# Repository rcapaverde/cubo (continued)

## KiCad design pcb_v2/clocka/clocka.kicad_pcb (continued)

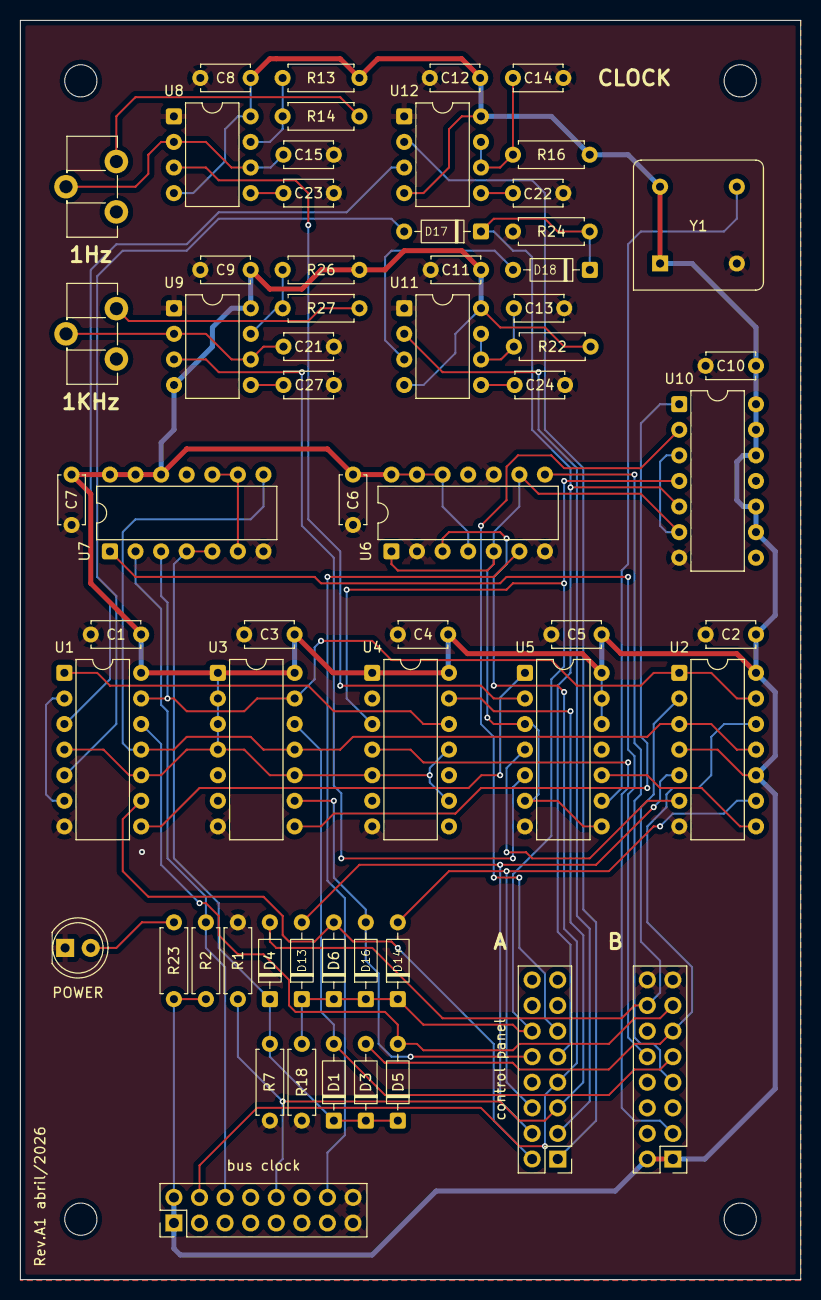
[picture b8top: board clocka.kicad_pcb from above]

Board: 2 copper layers, 77.5 x 125.0 mm, 61 parts (0 on the bottom side), 52 nets.

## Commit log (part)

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2025-12-11 arquivos que estavam no pc67
2025-12-11 interface serial
2025-12-12 arquivos no note
2025-12-12 arquivos do gdrive
2025-12-12 ignorar tambem os arquivos de backup do kicad
2025-12-14 adicionados o designador e o swap para a arquivo reg16
2025-12-21 alterando os pinos de alimentacao no conector
2025-12-23 projeto enviado para impressao em dezembro/25
2025-12-23 roteamento pronto e electric rules verificadas
2025-12-28 concluido o desenho das placas satelite do banco de registradores de 16 bits
2025-12-30 adicionados imagens 3D para os componentes customizados
2025-12-31 modelo 3d do interruptor; primeira versao do firmware do testbench (falta ainda converter o codigo para comunicar via latch)
2026-01-03 comunicacao com o LCD agora eh feita de forma direta, sem o uso de bibliotecas (necessario devido a conexao indireta com o controlador do LCD)
2026-01-03 versao B2 da testbench (com a alimentacao das placas de teste reposicionadas para as extremidades
2026-01-04 a interface com a sub8 parece incompativel; corrigindo a interface
2026-01-05 concluido o roteamento da revisao B1
2026-01-07 vias de alimentacao movidas para as extremidades do conector
2026-01-07 removidos os backups da pasta PCB
2026-01-12 correcao na pinagem do INA226 (SDA e SCL entravam nos pinos errados do arduino)
2026-01-12 ajustes para usar o multiplexador
2026-01-12 breakboards do edge socket para breadboard
2026-01-12 configuracoes para o jlcpcb
2026-01-12 inicio da revisao completa; a placa sr8 será removida e incorporada aqui
2026-01-15 revisao completa; mgrfa agora inclui sr8 e sgrda; remover estes dois no proximo commit
2026-01-16 Módulos SR8A e SGRDA incorporados ao MGRFA
2026-01-16 concluida a revisão
2026-01-16 entrada de força nas laterais; select agora é posicional, permitindo que a placa seja inserida em qualquer slot
2026-01-16 alimentação movida para as extremidades do conector
2026-01-22 deslocando alimentação para as estremidades do conector; carry out em três estados (ativo apenas quando select)
2026-01-22 faltava salvar
2026-01-22 carry out depende de select
2026-01-30 projeto não existe
2026-01-30 PCB concluída
2026-02-07 ajuste no espacamento entre os conectores flat
2026-02-07 correção no valor do resitor do led de power
2026-02-09 modelo 3d do display de 7 segmentos
2026-02-09 sketch de teste isolado da testbench-sub8 (comandada diretamente por um arduino)
2026-02-09 ainda pendente de conclusão do roteamento
2026-02-09 roteamento refeito; ainda pendente
2026-02-12 concluidas as modificações de layout na pcb
2026-02-13 mais alterações na pcb
2026-02-13 recomeçando o roteamento
2026-02-14 concluído o roteamento; falta corrigir os erros apontados pela validação de regras
2026-02-14 ajustes para envio para produção
2026-02-15 cartucho de rom
2026-02-16 gravador de rom, diretamente no cartucho
2026-02-16 controladora de memória
2026-02-16 roteamento com problemas; refazer
2026-02-17 concluído o roteamento
2026-02-18 inicio dos trabalhos na unidade de controle e lógica
2026-02-21 experimentação com opcodes
2026-02-22 continuando com a implementação da lógica de controle; ROM de ucode expandida para 17 bits
2026-02-24 alteração de layout
2026-02-27 revisando o ERC
2026-03-01 movendo itens da clu para o sysbus
2026-03-01 clock ainda está difícil; ioc está indo no caminho certo, mas falta definir a porta de controle para a serial
2026-03-04 placa clock gerando os sinais clock e n_clock sincronizados
2026-03-05 padronização de conector de IO; ideias para o layout do backplane
2026-03-08 definindo o layout para empilhar as placas
2026-03-09 ajustes de layout; nenhuma alteração na lógica
2026-03-10 adicionados os botões para clock manual
2026-03-10 refazendo os pcbs para caber em folha A4
2026-03-11 concluído o esquemático do clock; iniciando o layout do pcb a partir das dimensões definidas no croqui
2026-03-15 Separado o painel de controle do gerador de clock
2026-03-15 conclusão do teste
2026-03-16 layout do painel de controle do gerador de clock
2026-03-20 Adicionado a porta para clock out; trabalhando no roteamento
2026-03-21 layout de pcb do clock
2026-03-24 layout concluído
2026-03-24 pcb reduzida; iniciando um novo layout com inversão na posição dos chips
2026-03-24 novo layout do pcb
2026-03-24 Novo layout concluído
2026-03-30 conector reposicionado para ser compatível com a sysbus
2026-03-30 correção nos pinos
2026-03-30 posicionamento dos conectores com os demais módulos
2026-03-30 refazendo o módulo de registradores
2026-04-05 ajustes nos botões do painel de controle do clock
2026-04-05 implementação do firmware
2026-04-06 continuando implementação do clock
2026-04-11 desenho da chave de slide
2026-04-11 usando a nova chave de slide, posicionado a direita
2026-04-11 conectores do painel de controle posicionados na parte inferior, a direita; isso interfere com a passagem do cabo do clock
2026-04-11 conector para o painel de controle do clock reorientado para a vertical; cabos passarão pela lateral, farão curva de 90o e vão para frente
2026-04-14 definido o layout da placa com os sete registradores de 8 bits
2026-04-14 apenas questões estéticas
2026-04-16 reduzida a largura da pcb de clock, para sobrar mais espaço para a pcb de registradores
2026-04-17 Redimensionamento do clock para abrir mais espaço para os registradores
2026-04-18 concluida a versao com teste de tbsub8
2026-04-19 layout de pcb pronto para fabricação
2026-04-20 concluído o layout da pcb
2026-04-20 ULA reduzida de tamanho, para sobrar mais espaço para a CL
2026-04-20 inicio de layout da CL
2026-04-21 layout avançando
2026-04-21 reposicionado o conector para a ULA
2026-04-21 atualização de tamanho e posição de conectores
2026-04-22 novos sinais
2026-04-22 esquemático simplificado; a rom é muito lenta, endereço de escrita pode ser setado a cada ciclo
2026-04-23 ajuste nos sinais do microcódigo
2026-04-23 correções no esquemático e reiniciando o pcb
2026-04-23 validação da lógica da unidade de controle e lógica
2026-04-24 avançando na análise da lógica; correções de problema já detectados
2026-04-24 problema no restart cycle quando a instrução executa em três ciclos (ou seja, sem um restart cycle explícito no microcódigo
2026-04-27 mais simulações e ajustes no pcb; falta o sinal de WRITE durante o reset e interrupt
2026-04-29 inversão dos sinais de seleção de step para simplificar o circuito
2026-05-02 finalizado o layout e testes lógicos do pcb
2026-05-02 novo sinal no opcode
2026-05-03 ajustes no layout da pcb
2026-05-03 inicio do layout da pcb
2026-05-04 concluída a primeira versão do layout do pcb; rever o circuito de reset
2026-05-04 revisão na posição dos conectores
2026-05-05 melhoria no reset, para que seja acionado automaticamente ao ligar
2026-05-05 inversão na posição dos conectores, para coincidir com o sysbus
2026-05-07 posicionamento de furos e conectores que faltavam
2026-05-07 redimensionamento do pcb e início do layout
2026-05-07 furação para suporte
2026-05-10 concluído o layout do pcb
2026-05-10 algumas simplificações
2026-05-11 case do cartucho
2026-05-15 complementos do case
2026-05-15 layout do pcb já considerando as dimensões corretas
2026-05-15 ajustes de layout
2026-05-16 tamanho dos conectores estava errado
2026-05-16 cartucho 90 graus
2026-05-17 usando um componente com as dimensões do conector de cabo flat, para impedir erros de posicionamento
2026-05-18 atualização do conector flat
2026-05-19 reset do flag int_mask vinculado a execução de opcode_int
2026-05-23 adicionado teste para a clock cp
2026-05-24 Correção no lado de conexão dos pinos
2026-05-24 correções no esquemático e pcb
2026-05-25 base para construção do protótipo
2026-05-25 preparação para produção
2026-05-31 concluido o novo layout
2026-06-01 novo layout para ajustar a pinagem do conector
2026-06-11 layout já em V3 do módulo de registradores
2026-06-13 iniciando o asm para o instruction set v4
2026-06-14 nova implementação do assembler para instruction set v4
2026-06-19 novo layout para pcb v3
2026-06-20 avançando o layout da placa com os registradores
2026-06-21 finalização da primeira fase de layout do pcb
2026-06-28 avançado na otimização do pcb
2026-06-28 concluida a primeira rodada de layout do pcb; removidas conexões de cascateamento de decremento para os registradores que não tenham esta função
2026-06-28 mais ajustes no layout
